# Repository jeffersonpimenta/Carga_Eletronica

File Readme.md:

Projeto de uma carga eletrônica inteligente (electronic load) apresentado como trabalho de fim de curso pela Universidade Federal do Ceará.

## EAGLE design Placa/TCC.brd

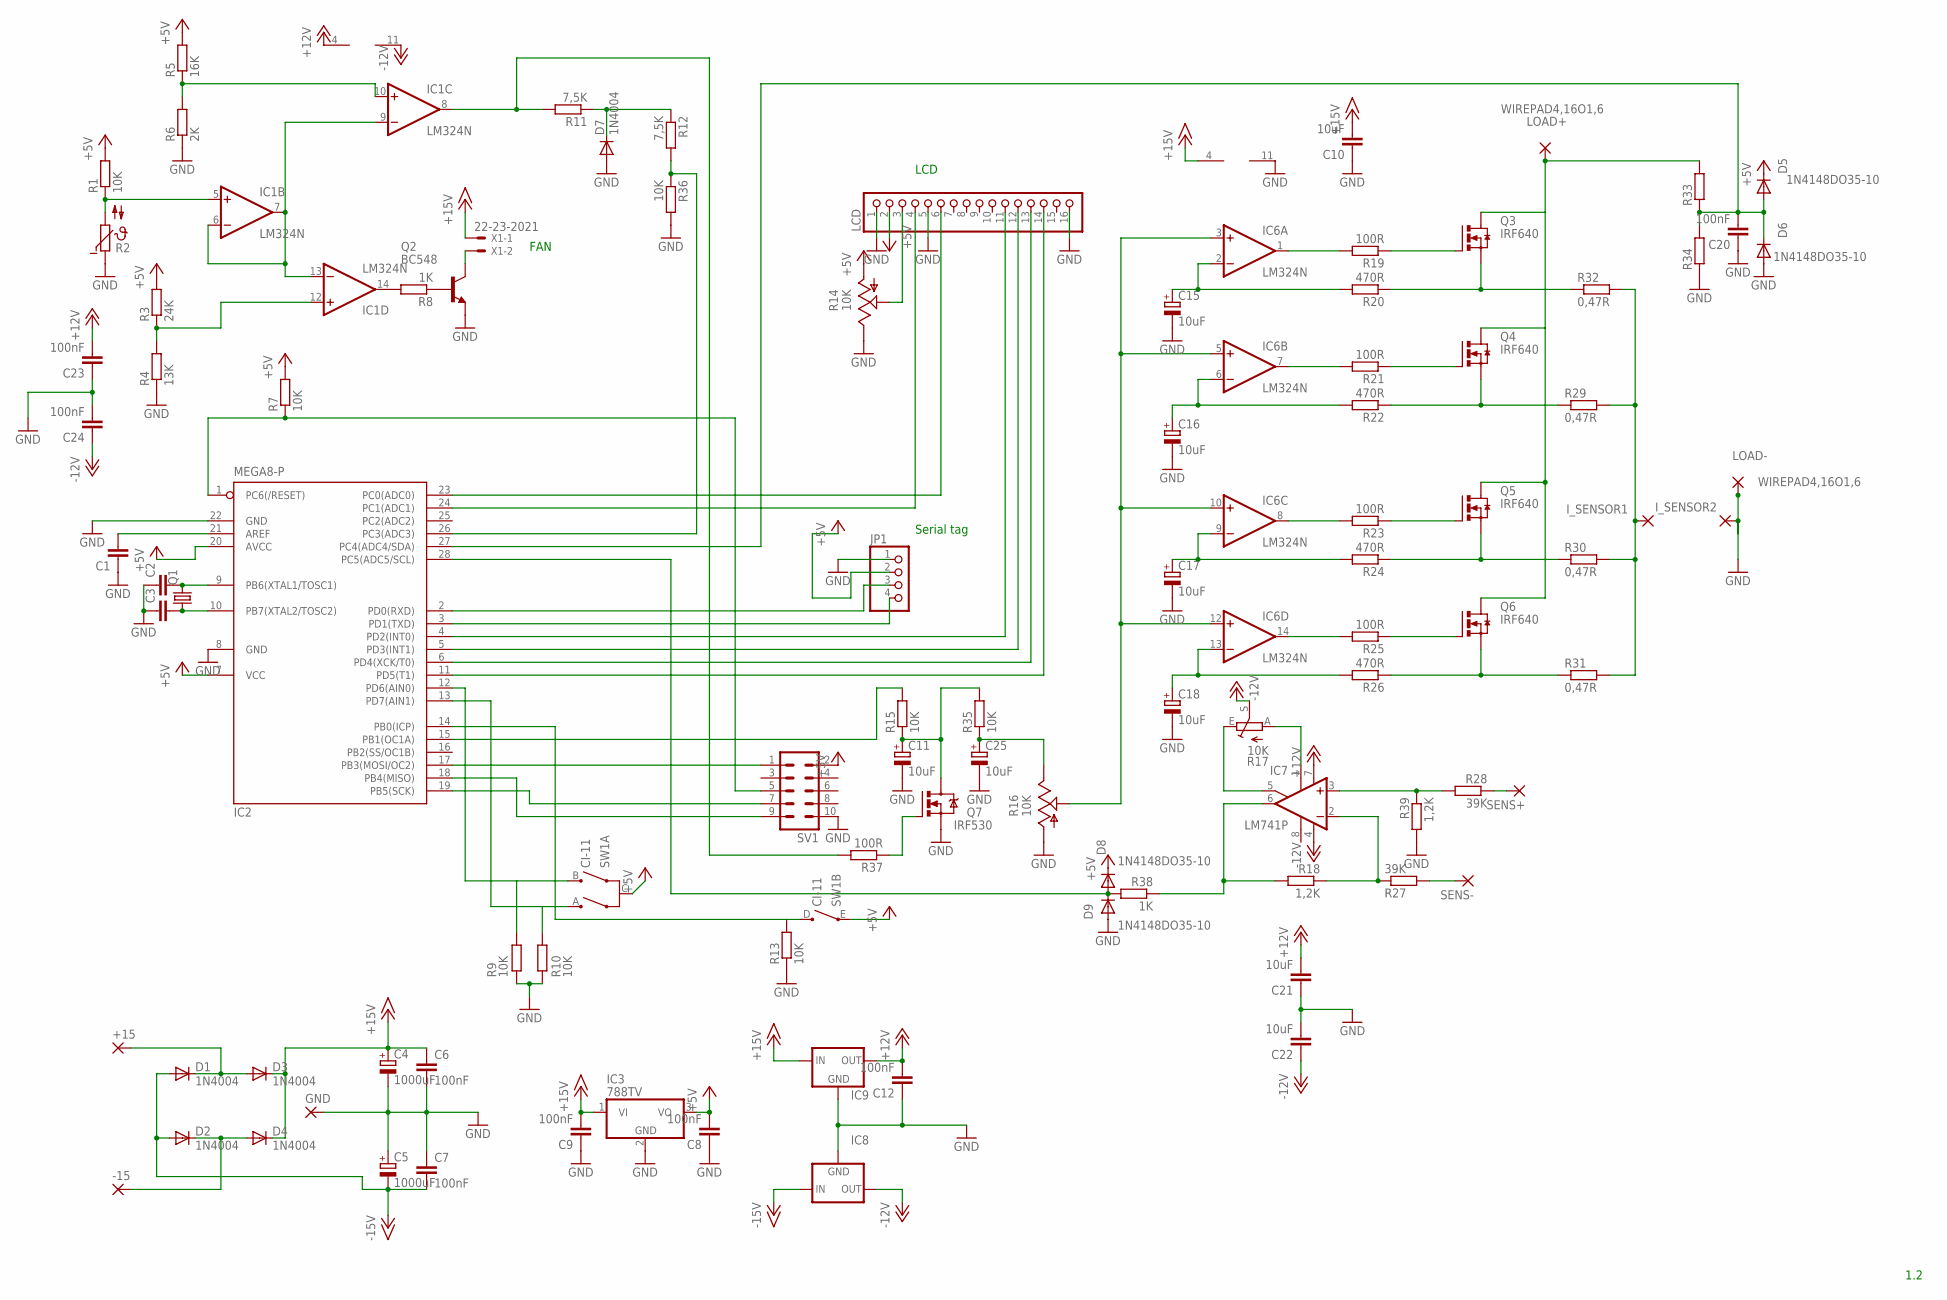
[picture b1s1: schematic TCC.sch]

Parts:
+15: 2,54/0,9
-15: 2,54/0,9
C1, C2, C3: C5/2.5; C5B2.5
C4, C5: 1000uF; E3,5-10
C6, C7: 100nF; C050-025X075
C8, C9, C12, C20, C23, C24: 100nF; C5B2.5
C10, C21, C22: 10uF; C5B2.5
C11, C15, C16, C17, C18, C25: 10uF; E2,5-6E
D1, D2, D3, D4, D7: 1N4004; DO41-10
D5, D6, D8, D9: 1N4148DO35-10; DO35-10
GND: 2,54/0,9
IC1, IC6: LM324N; DIL14
IC2: MEGA8-P; DIL28-3
IC3: 788TV; TO220V
IC7: LM741P; DIL08
IC8: 79XXS
IC9: 78XXS
I_SENSOR1, I_SENSOR2: 3,17/1,3
JP1: PINHD-1X4; 1X04
LCD: PINHD-1X16; 1X16
LOAD+: WIREPAD4,16O1,6; 4,16O1,6
LOAD-: WIREPAD4,16O1,6; 4,16O1,6
Q1: CRYSTALHC49S; HC49/S
Q2: BC548; TO92-EBC
Q3, Q4, Q5, Q6: IRF640; TO220BH
Q7: IRF530; TO220BV
R1: 10K; 0207/12
R2: NTC640; P640
R3: 24K; 0207/10
R4: 13K; 0204/7
R5: 16K; 0204/7
R6: 2K; 0204/7
R7, R9, R10, R15, R35, R36: 10K; 0204/7
R8: 1K; 0204/7
R11, R12: 7,5K; 0204/7
R13: 10K; 0207/10
R14: 10K; LI10@1
R16: 10K; S64W
R17: 10K; LI10
R18, R39: 1,2K; 0207/10
R19, R25: 100R; 0207/10
R20, R24, R26: 470R; 0207/10
R21, R23: 100R; 0207/15
R22: 470R; 0207/12
R27: 39K; 0207/10
R28: 39K; 0204/7
R29, R30, R31, R32: 0,47R; VTA56
R33: R-EU_0207/15; 0207/15
R34: R-EU_0207/10; 0207/10
R37: 100R; 0204/7
R38: 1K; 0207/10
SENS+: 2,54/1,1
SENS-: 2,54/1,1
SV1: ML10
SW1: CI-11
X1: 22-23-2021

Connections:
+5V: C8.2, D5.C, D8.C, IC2.7 (VCC), IC2.20 (AVCC), IC3.3 (VO), JP1.2, LCD.2, R1.2, R3.2, R5.2, R7.2, R14.A, SV1.2, SW1.C, SW1.E
+12V: C12.2, C21.2, C23.2, IC1.4 (V+), IC7.7 (V+), IC9.OUT
+15V: C4.+, C6.1, C9.2, C10.2, D3.C, D4.C, IC3.1 (VI), IC6.4 (V+), IC9.IN, X1.1
-12V: C22.1, C24.1, IC1.11 (V-), IC7.4 (V-), IC8.OUT, R17.S
-15V: C5.-, C7.2, D1.A, D2.A, IC8.IN
GND: C1.1, C2.1, C3.1, C4.-, C5.+, C6.2, C7.1, C8.1, C9.1, C10.1, C11.-, C12.1, C15.-, C16.-, C17.-, C18.-, C20.1, C21.1, C22.2, C23.1, C24.2, C25.-, D6.A, D7.A, D9.A, GND.1, IC2.8 (GND), IC2.22 (GND), IC3.2 (GND), IC6.11 (V-), IC8.GND, IC9.GND, I_SENSOR2.1, JP1.1, LCD.1, LCD.5, LCD.16, LOAD-.1, Q2.E, Q7.S, R2.1, R4.1, R6.1, R9.1, R10.1, R13.1, R14.E, R16.A, R34.1, R36.2, R39.2, SV1.10
unnamed: C2.2, IC2.9 (PB6(XTAL1/TOSC1)), Q1.2
unnamed: C3.2, IC2.10 (PB7(XTAL2/TOSC2)), Q1.1
unnamed: IC2.17 (PB3(MOSI/OC2)), SV1.1
unnamed: IC2.18 (PB4(MISO)), SV1.9
unnamed: IC2.19 (PB5(SCK)), SV1.7
unnamed: IC2.1 (PC6(/RESET)), R7.1, SV1.5
unnamed: C1.2, IC2.21 (AREF)
unnamed: IC1.8 (OUT), R11.2, R37.2
unnamed: IC2.24 (PC1(ADC1)), LCD.4
unnamed: IC2.23 (PC0(ADC0)), LCD.6
unnamed: IC2.4 (PD2(INT0)), LCD.11
unnamed: IC2.5 (PD3(INT1)), LCD.12
unnamed: IC2.14 (PB0(ICP)), R13.2, SW1.D
unnamed: IC2.11 (PD5(T1)), LCD.14
unnamed: IC2.12 (PD6(AIN0)), R9.2, SW1.B
unnamed: C11.+, Q7.D, R15.1, R35.2
unnamed: Q3.S, R20.1, R32.1
unnamed: Q4.S, R22.1, R29.1
unnamed: Q5.S, R24.1, R30.1
unnamed: IC2.13 (PD7(AIN1)), R10.2, SW1.A
unnamed: Q6.S, R26.1, R31.1
unnamed: IC6.1 (OUT), R19.2
unnamed: Q3.G, R19.1
unnamed: IC6.7 (OUT), R21.2
unnamed: Q4.G, R21.1
unnamed: LOAD+.1, Q3.D, Q4.D, Q5.D, Q6.D, R33.2
unnamed: IC6.3 (+IN), IC6.5 (+IN), IC6.10 (+IN), IC6.12 (+IN), R16.S
unnamed: C15.+, IC6.2 (-IN), R20.2
unnamed: C17.+, IC6.9 (-IN), R24.2
unnamed: C16.+, IC6.6 (-IN), R22.2
unnamed: IC7.2 (-IN), R18.1, R27.1
unnamed: IC1.6 (-IN), IC1.7 (OUT), IC1.9 (-IN), IC1.13 (-IN)
unnamed: C18.+, IC6.13 (-IN), R26.2
unnamed: D8.A, D9.C, IC2.28 (PC5(ADC5/SCL)), R38.2
unnamed: IC7.1 (ON1), R17.A
unnamed: C25.+, R16.E, R35.1
unnamed: IC2.15 (PB1(OC1A)), R15.2
unnamed: IC7.5 (ON2), R17.E
unnamed: C20.2, D5.A, D6.C, IC2.27 (PC4(ADC4/SDA)), R33.1, R34.2
unnamed: LCD.3, R14.S
unnamed: IC1.5 (+IN), R1.1, R2.2
unnamed: IC1.10 (+IN), R5.1, R6.2
unnamed: IC7.3 (+IN), R28.2, R39.1
unnamed: Q2.B, R8.1
unnamed: IC2.26 (PC3(ADC3)), R12.2, R36.1
unnamed: Q2.C, X1.2
unnamed: IC1.14 (OUT), R8.2
unnamed: IC1.12 (+IN), R3.1, R4.2
unnamed: I_SENSOR1.1, R29.2, R30.2, R31.2, R32.2
unnamed: IC2.6 (PD4(XCK/T0)), LCD.13
unnamed: IC6.8 (OUT), R23.2
unnamed: Q5.G, R23.1
unnamed: IC6.14 (OUT), R25.2
unnamed: Q6.G, R25.1
unnamed: Q7.G, R37.1
unnamed: D7.C, R11.1, R12.1
unnamed: +15.1, D1.C, D3.A
unnamed: -15.1, D2.C, D4.A
unnamed: IC7.6 (OUT), R18.2, R38.1
unnamed: R27.2, SENS-.1
unnamed: R28.1, SENS+.1
unnamed: IC2.3 (PD1(TXD)), JP1.4
unnamed: IC2.2 (PD0(RXD)), JP1.3

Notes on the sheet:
1.2
Serial tag
LCD
FAN

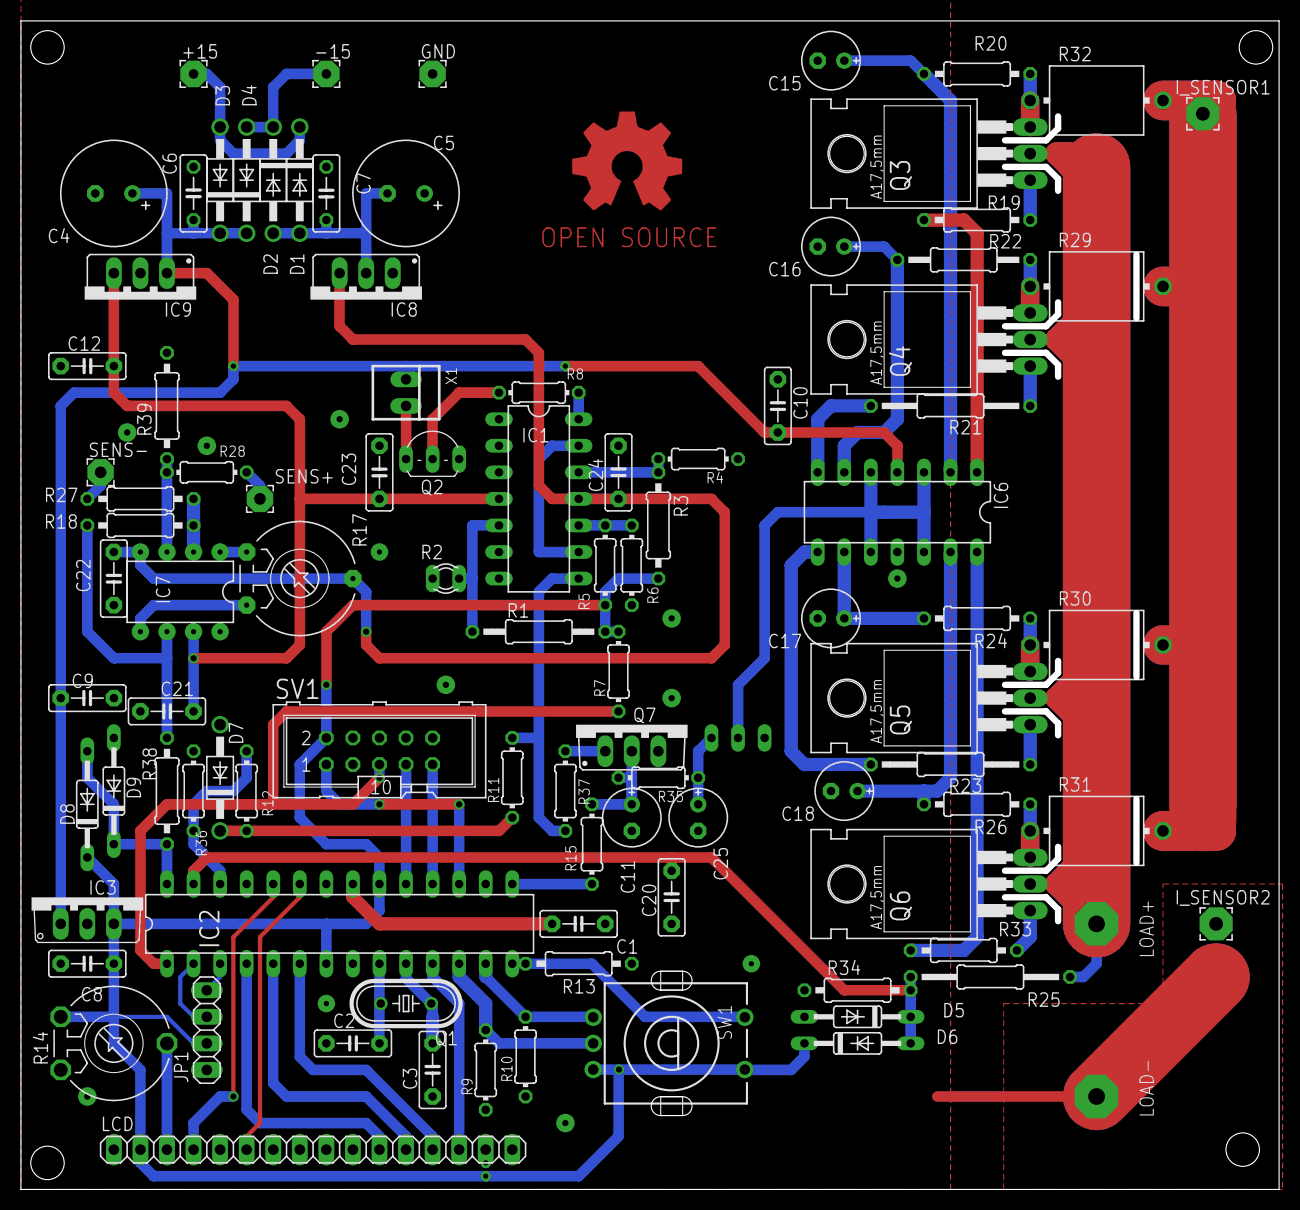
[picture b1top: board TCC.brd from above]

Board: 2 copper layers, 119.7 x 111.1 mm, 98 parts (1 on the bottom side), 69 nets.
